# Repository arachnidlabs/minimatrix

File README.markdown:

# Minimatrix

Minimatrix is a teeny little backpack for 3cm monocolor LED matrixes. It plays animations, and is reprogrammable via your computer monitor!

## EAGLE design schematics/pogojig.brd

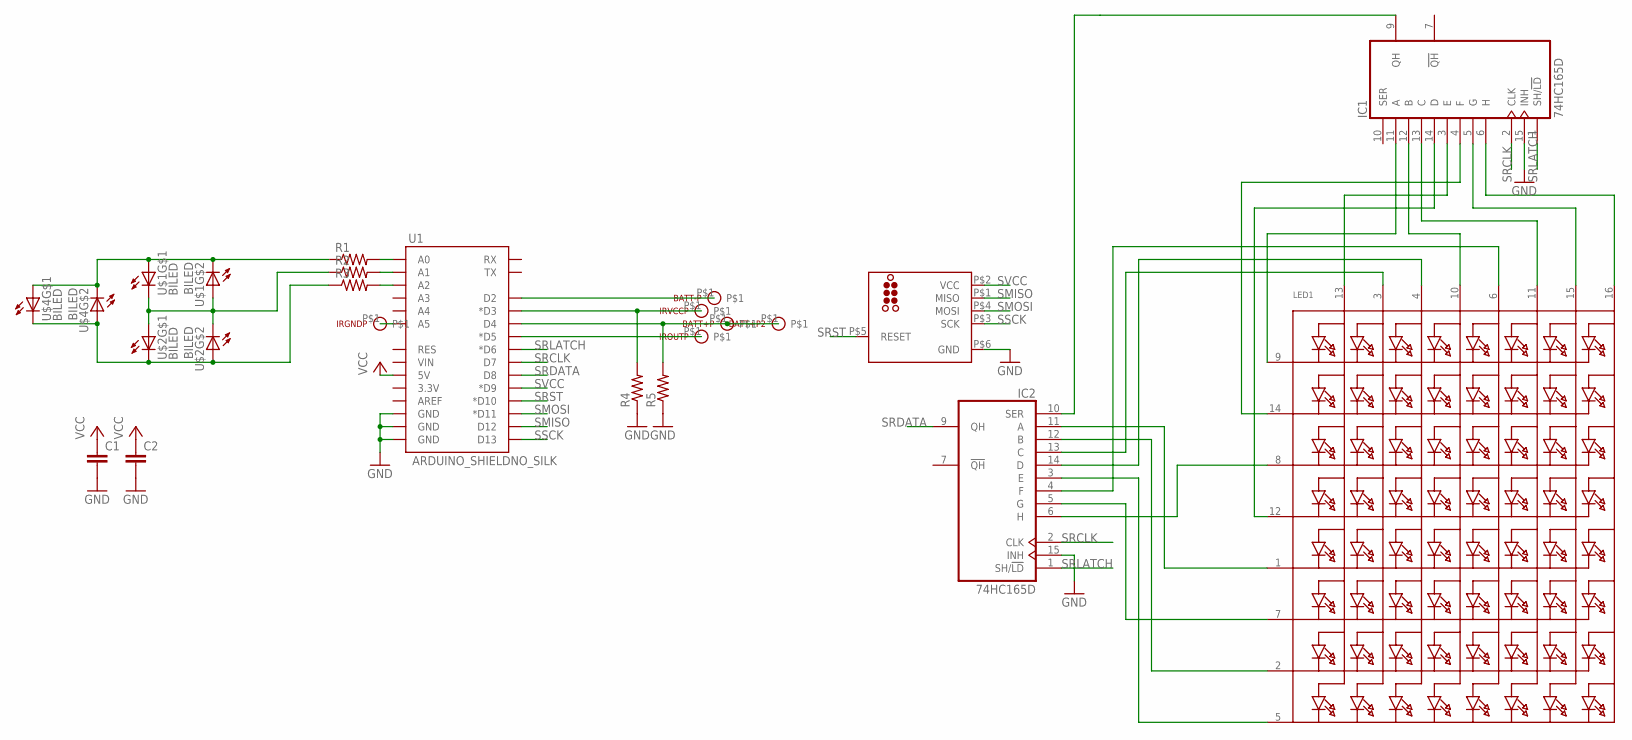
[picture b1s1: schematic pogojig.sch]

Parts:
BATT+P, BATT+P2: POGOPIN1.02; POGOPIN-1.02
BATT-P: POGOPIN1.02; POGOPIN-1.02
C1, C2: CAP0805; 0805
IC1, IC2: 74HC165D; SO16
IRGNDP: POGOPIN1.02; POGOPIN-1.02
IROUTP: POGOPIN1.02; POGOPIN-1.02
IRVCCP: POGOPIN1.02; POGOPIN-1.02
LED1: SEGMENT_8X8_ROWCATHODE; SEGMENT-30MM-POGO
R1, R2, R3, R4, R5: RESISTOR0805-RES; 0805
U1: ARDUINO_SHIELDNO_SILK; DUEMILANOVE_VIAS
U$1, U$2, U$4: BILED
U$3: TC2030_AVR; TC2030-MCP-NL-POGO

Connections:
GND: C1.2, C2.2, IC1.8 (GND), IC1.15 (INH), IC2.8 (GND), IC2.15 (INH), R4.1, R5.1, U1.GND@0 (GND), U1.GND@1 (GND), U1.GND@2 (GND), U$3.P$6 (GND)
unnamed: IC2.11 (A), LED1.1 (K5)
unnamed: IC2.12 (B), LED1.2 (K7)
unnamed: IC2.13 (C), LED1.3 (A2)
unnamed: IC2.14 (D), LED1.4 (A3)
unnamed: IC2.3 (E), LED1.5 (K8)
unnamed: IC2.4 (F), LED1.6 (A5)
unnamed: IC1.14 (D), LED1.12 (K4)
unnamed: IC2.5 (G), LED1.7 (K6)
unnamed: IC2.6 (H), LED1.8 (K3)
unnamed: IC1.11 (A), LED1.9 (K1)
unnamed: IC1.12 (B), LED1.10 (A4)
unnamed: IC1.13 (C), LED1.11 (A6)
unnamed: IC1.3 (E), LED1.13 (A1)
unnamed: IC1.4 (F), LED1.14 (K2)
unnamed: IC1.5 (G), LED1.15 (A7)
unnamed: IC1.6 (H), LED1.16 (A8)
unnamed: IC1.9 (QH), IC2.10 (SER)
unnamed: IRGNDP.P$1, U1.A5
unnamed: BATT+P.P$1, BATT+P2.P$1, R5.2, U1.D4
unnamed: BATT-P.P$1, U1.D2
unnamed: IRVCCP.P$1, R4.2, U1.D3 (*D3)
unnamed: IROUTP.P$1, U1.D5 (*D5)
unnamed: R3.2, U1.A2
unnamed: R2.2, U1.A1
unnamed: R1.2, U1.A0
unnamed: R3.1, U$2.A2 (A), U$2.C1 (C), U$4.A2 (A), U$4.C1 (C)
unnamed: R1.1, U$1.A1 (A), U$1.C2 (C), U$4.A1 (A), U$4.C2 (C)
unnamed: R2.1, U$1.A2 (A), U$1.C1 (C), U$2.A1 (A), U$2.C2 (C)
SMISO: U1.D12, U$3.P$1 (MISO)
SMOSI: U1.D11 (*D11), U$3.P$4 (MOSI)
SRCLK: IC1.2 (CLK), IC2.2 (CLK), U1.D7
SRDATA: IC2.9 (QH), U1.D8
SRLATCH: IC1.1 (SH/!LD), IC2.1 (SH/!LD), U1.D6 (*D6)
SRST: U1.D10 (*D10), U$3.P$5 (RESET)
SSCK: U1.D13, U$3.P$3 (SCK)
SVCC: U1.D9 (*D9), U$3.P$2 (VCC)
VCC: C1.1, C2.1, IC1.16 (VCC), IC2.16 (VCC), U1.5V

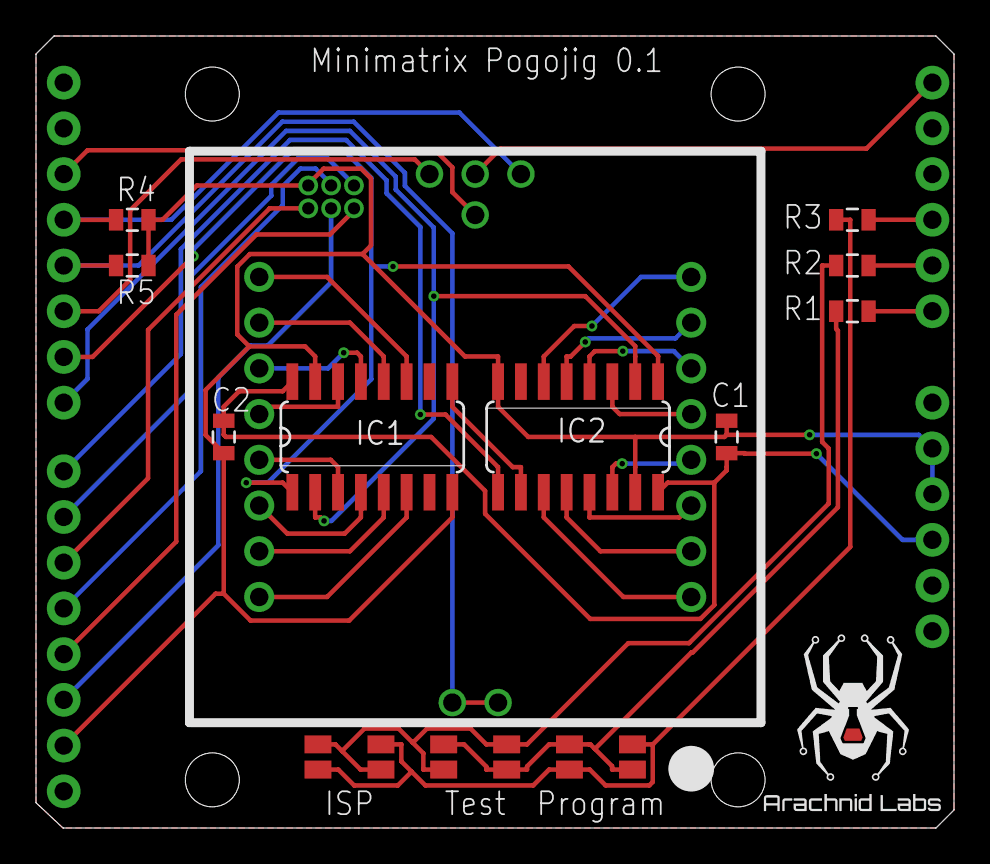
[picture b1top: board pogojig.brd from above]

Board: 2 copper layers, 51.0 x 44.0 mm, 22 parts (1 on the bottom side), 38 nets.

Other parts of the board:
U$5: ARACHNID_LABS_LOGO_SM

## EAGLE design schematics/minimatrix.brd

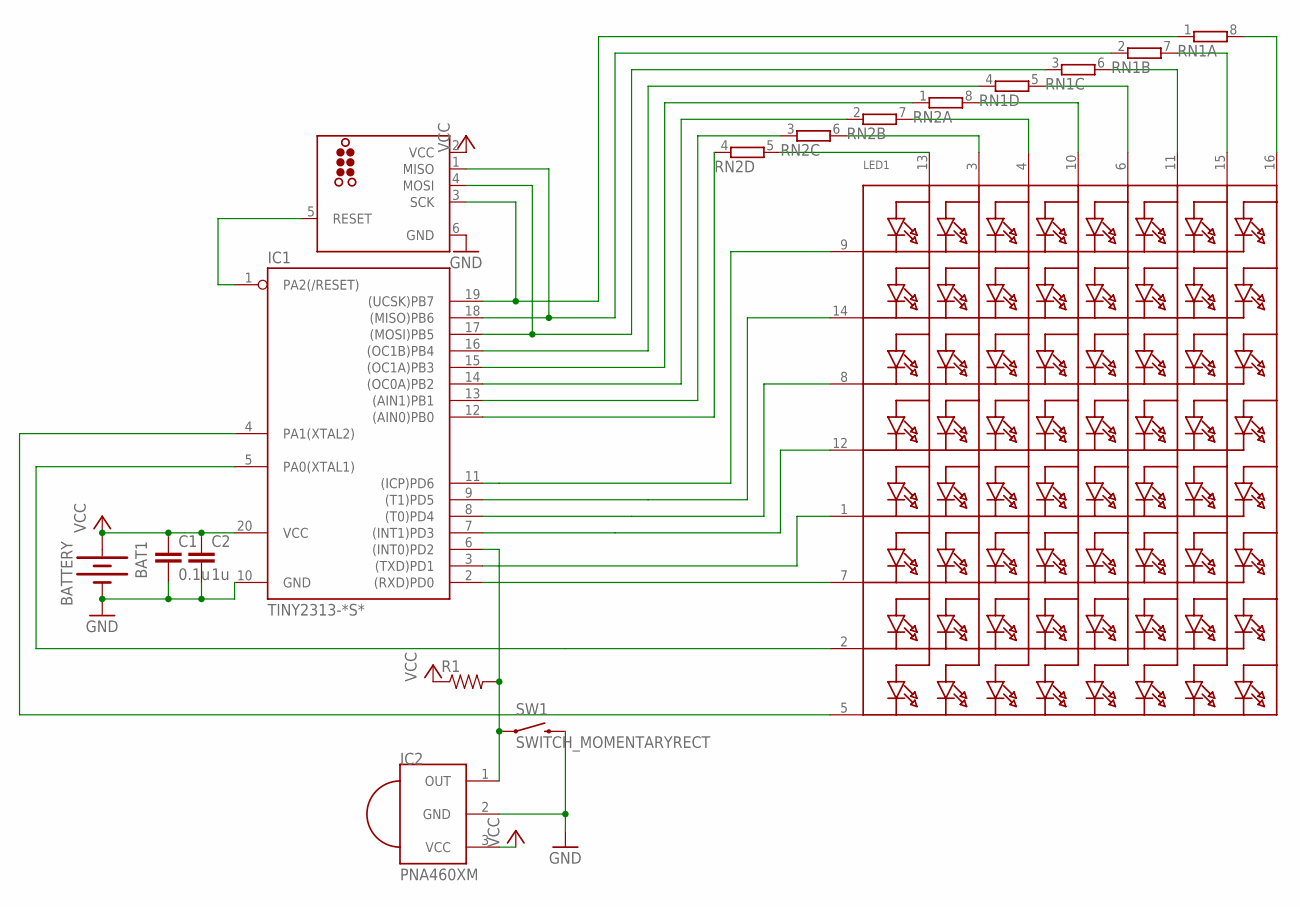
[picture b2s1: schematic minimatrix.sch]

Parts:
BAT1: BATTERY; COINCELL_PTH
C1: 0.1u; 0805
C2: 1u; 0805
IC1: TINY2313-*S*; SO20L$
IC2: PNA460XM
LED1: SEGMENT_8X8_ROWCATHODEM12A881UR; SEGMENT_BL-M12A881UR
R1: RESISTOR0805-RES; 0805
RN1, RN2: 4R-NCAY16; CAY16
SW1: SWITCH_MOMENTARYRECT; SWITCH_MOMENTARY_RECT
U$3: TC2030_AVRMCP-NL; TC2030-MCP-NL

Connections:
C2: IC1.13 ((AIN1)PB1), RN2.3 (1)
C3: IC1.14 ((OC0A)PB2), RN2.2 (1)
C4: IC1.15 ((OC1A)PB3), RN2.1
C5: IC1.16 ((OC1B)PB4), RN1.4 (1)
COL1: IC1.12 ((AIN0)PB0), RN2.4 (1)
GND: BAT1.NEG (-), C1.2, C2.2, IC1.10 (GND), IC2.2 (GND), SW1.P$2 (2), U$3.6 (GND)
MISO: IC1.18 ((MISO)PB6), RN1.2 (1), U$3.1 (MISO)
MOSI: IC1.17 ((MOSI)PB5), RN1.3 (1), U$3.4 (MOSI)
unnamed: IC1.2 ((RXD)PD0), LED1.7 (K6)
unnamed: LED1.3 (A2), RN2.6 (2)
unnamed: LED1.4 (A3), RN2.7 (2)
unnamed: LED1.10 (A4), RN2.8 (2)
unnamed: LED1.6 (A5), RN1.5 (2)
unnamed: LED1.11 (A6), RN1.6 (2)
unnamed: LED1.15 (A7), RN1.7 (2)
unnamed: LED1.16 (A8), RN1.8 (2)
unnamed: LED1.13 (A1), RN2.5 (2)
unnamed: IC1.3 ((TXD)PD1), LED1.1 (K5)
unnamed: IC1.4 (PA1(XTAL2)), LED1.5 (K8)
unnamed: IC1.6 ((INT0)PD2), IC2.1 (OUT), R1.2, SW1.P$1 (1)
R2: IC1.9 ((T1)PD5), LED1.14 (K2)
R3: IC1.8 ((T0)PD4), LED1.8 (K3)
R4: IC1.7 ((INT1)PD3), LED1.12 (K4)
R7: IC1.5 (PA0(XTAL1)), LED1.2 (K7)
RESET: IC1.1 (PA2(/RESET)), U$3.5 (RESET)
ROW1: IC1.11 ((ICP)PD6), LED1.9 (K1)
SCK: IC1.19 ((UCSK)PB7), RN1.1, U$3.3 (SCK)
VCC: BAT1.POS1 (+), BAT1.POS2 (+), C1.1, C2.1, IC1.20 (VCC), IC2.3 (VCC), R1.1, U$3.2 (VCC)

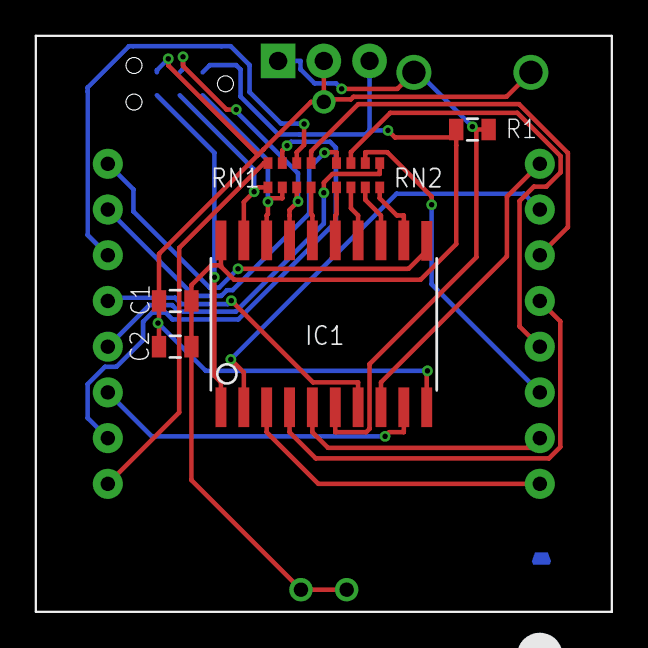
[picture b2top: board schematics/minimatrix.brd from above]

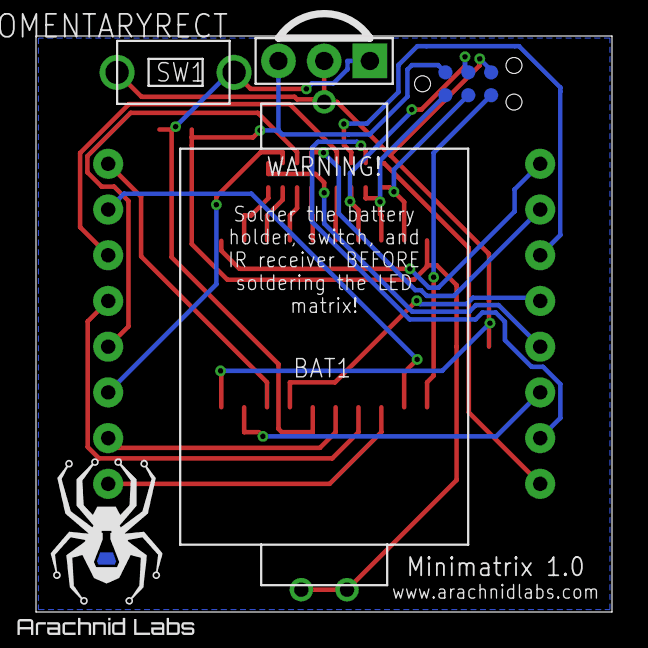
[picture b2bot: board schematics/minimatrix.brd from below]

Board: 2 copper layers, 32.0 x 32.0 mm, 12 parts (5 on the bottom side), 28 nets.

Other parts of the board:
U$4: ARACHNID_LABS_LOGO_SM

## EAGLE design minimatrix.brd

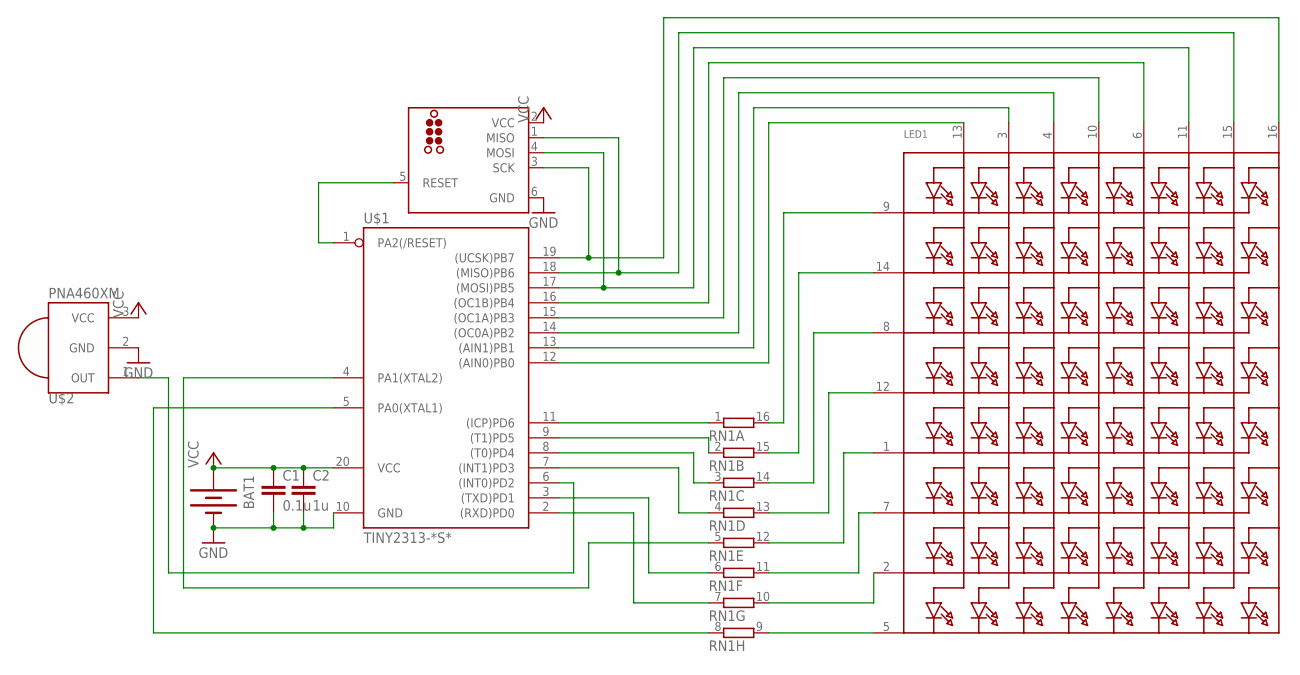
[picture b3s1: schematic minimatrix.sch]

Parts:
BAT1: BATTERY20MM_4LEGS; BATTCON_20MM_4LEGS
C1: 0.1u; 0805
C2: 1u; 0805
LED1: SEGMENT_8X8_ROWCATHODEM12A881UR; SEGMENT_BL-M12A881UR
RN1: 8R-NEXB2HV; EXB2HV
U$1: TINY2313-*S*; SO20L$
U$2: PNA460XM
U$3: TC2030_AVRMCP-NL; TC2030-MCP-NL

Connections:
C1: LED1.13 (A1), U$1.12 ((AIN0)PB0)
C2: LED1.3 (A2), U$1.13 ((AIN1)PB1)
C3: LED1.4 (A3), U$1.14 ((OC0A)PB2)
C4: LED1.10 (A4), U$1.15 ((OC1A)PB3)
C5: LED1.6 (A5), U$1.16 ((OC1B)PB4)
C6: LED1.11 (A6), U$1.17 ((MOSI)PB5), U$3.4 (MOSI)
C7: LED1.15 (A7), U$1.18 ((MISO)PB6), U$3.1 (MISO)
C8: LED1.16 (A8), U$1.19 ((UCSK)PB7), U$3.3 (SCK)
GND: BAT1.2 (-), C1.2, C2.2, U$1.10 (GND), U$2.2 (GND), U$3.6 (GND)
unnamed: U$1.6 ((INT0)PD2), U$2.1 (OUT)
unnamed: U$1.1 (PA2(/RESET)), U$3.5 (RESET)
unnamed: RN1.5 (1), U$1.4 (PA1(XTAL2))
R1: RN1.1, U$1.11 ((ICP)PD6)
R2: RN1.2 (1), U$1.9 ((T1)PD5)
R3: RN1.3 (1), U$1.8 ((T0)PD4)
R4: RN1.4 (1), U$1.7 ((INT1)PD3)
R6: RN1.6 (1), U$1.3 ((TXD)PD1)
R7: RN1.7 (1), U$1.2 ((RXD)PD0)
R8: RN1.8 (1), U$1.5 (PA0(XTAL1))
ROW1: LED1.9 (K1), RN1.16 (2)
ROW2: LED1.14 (K2), RN1.15 (2)
ROW3: LED1.8 (K3), RN1.14 (2)
ROW4: LED1.12 (K4), RN1.13 (2)
ROW5: LED1.1 (K5), RN1.12 (2)
ROW6: LED1.7 (K6), RN1.11 (2)
ROW7: LED1.2 (K7), RN1.10 (2)
ROW8: LED1.5 (K8), RN1.9 (2)
VCC: BAT1.1 (+), C1.1, C2.1, U$1.20 (VCC), U$2.3 (VCC), U$3.2 (VCC)

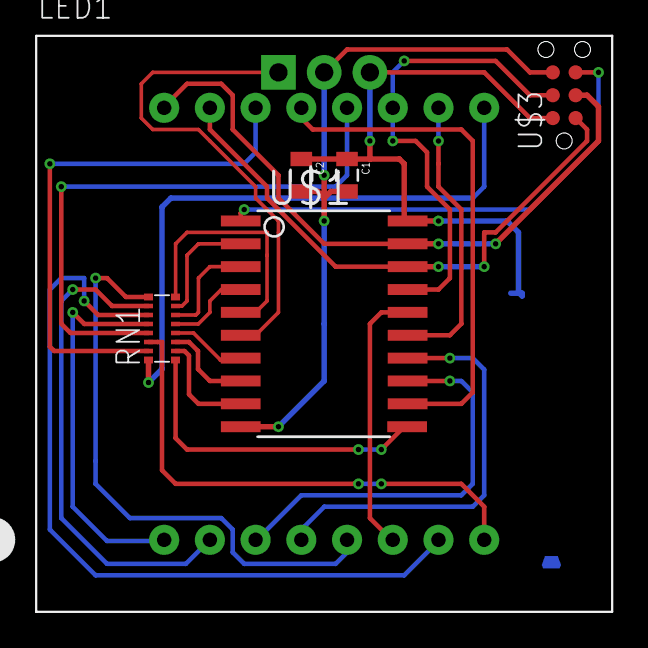
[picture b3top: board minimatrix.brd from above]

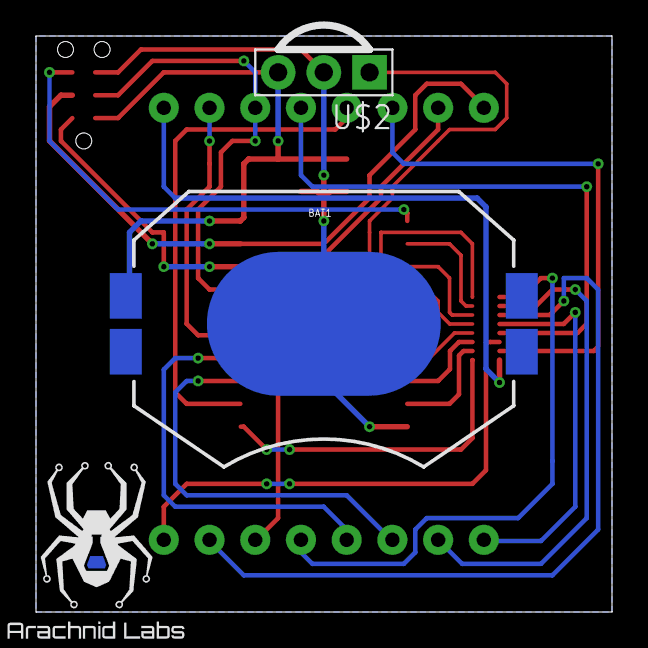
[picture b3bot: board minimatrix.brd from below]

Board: 2 copper layers, 32.0 x 32.0 mm, 9 parts (3 on the bottom side), 28 nets.

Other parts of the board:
U$4: ARACHNID_LABS_LOGO_SM

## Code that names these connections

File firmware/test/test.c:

#define F_CPU 8000000UL  // 8 MHz

#include <inttypes.h>
#include <avr/io.h>
#include <avr/pgmspace.h>
#include <avr/sleep.h>
#include <util/delay.h>
#include <avr/interrupt.h>

#include "../src/hardware.h"

static void ioinit(void) {
	// Set rows and columns as output
	COLUMN_DDR = 0xff;
	DDRD |= PORTD_ROWS;
	DDRA |= PORTA_ROWS;
//	PORTB = 0x255;
//	PORTD |= PORTD_ROWS;
//	PORTA |= PORTA_ROWS;

	sei();
}

struct {
	volatile uint8_t *port;
	uint8_t pin;
} out_pins[] = {
	{&PORTD, _BV(PD1)},
	{&PORTA, _BV(PA0)},
	{&PORTB, _BV(PB1)},
	{&PORTB, _BV(PB2)},
	{&PORTA, _BV(PA1)},
	{&PORTB, _BV(PB4)},
	{&PORTD, _BV(PD0)},
	{&PORTD, _BV(PD4)},
	{&PORTD, _BV(PD6)},
	{&PORTB, _BV(PB3)},
	{&PORTB, _BV(PB5)},
	{&PORTD, _BV(PD3)},
	{&PORTB, _BV(PB0)},
	{&PORTD, _BV(PD5)},
	{&PORTB, _BV(PB6)},
	{&PORTB, _BV(PB7)},
};

static uint8_t num_pins = 16;

void main(void) __attribute__((noreturn));

void main(void) {
	ioinit();

	int idx = 6;
	while(1) {
		// Wait for rising edge on IR PIN
		while(!(PIND & _BV(IR_PIN)));

		*out_pins[idx].port &= ~out_pins[idx].pin;
		idx = (idx + 1) % num_pins;
		*out_pins[idx].port |= out_pins[idx].pin;

		// Wait for falling edge on IR PIN
		while(PIND & _BV(IR_PIN));
	}
}

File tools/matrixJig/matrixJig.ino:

// Standalone AVR ISP programmer
// Modified July 2013 by Nick Johnson <nick@arachnidlabs.com>
// August 2011 by Limor Fried / Ladyada / Adafruit
// Jan 2011 by Bill Westfield ("WestfW")
//
// this sketch allows an Arduino to program a flash program
// into any AVR if you can fit the HEX file into program memory
// No computer is necessary. Two LEDs for status notification
// Press button to program a new chip. Piezo beeper for error/success 
// This is ideal for very fast mass-programming of chips!
//
// It is based on AVRISP
//
// using the following pins:
// 10: slave reset
// 11: MOSI
// 12: MISO
// 13: SCK
// ----------------------------------------------------------------------
#include <avr/pgmspace.h>
#include "optiLoader.h"
#include "SPI.h"

// Global Variables
int pmode=0;
byte pageBuffer[64];		       /* One page of flash */


/*
 * Pins to target
 */
#define SCK 13
#define MISO 12
#define MOSI 11
#define RESET 10
#define TARGET_POWER 9

#define PIN_BATT_NEG 2
#define PIN_BATT_POS 4
#define PIN_IRVCC 3
#define PIN_IROUT 5
#define PIN_SRLATCH 6
#define PIN_SRCLK 7
#define PIN_SRDATA 8

#define ISP_OK A2, A1, A0
#define ISP_BAD A1, A2, A0
#define TEST_OK A1, A0, A2
#define TEST_BAD A0, A1, A2
#define PROG_OK A2, A0, A1
#define PROG_BAD A0, A2, A1

void slow_down(boolean enable) {
  static uint16_t saved_ubrr;
  static boolean slow = false;

  // If we're already in the mode we're asking for, do nothing.  
  if(enable == slow) return;
  
  cli();
  if(enable) {
    CLKPR = _BV(CLKPCE);
    CLKPR = 0x1;
    saved_ubrr = (UBRR0H << 8) | UBRR0L;
    UBRR0H = saved_ubrr >> 9;
    UBRR0L = (saved_ubrr >> 1) & 0xFF;
    slow = true;
  } else {
    CLKPR = _BV(CLKPCE);
    CLKPR = 0x0;
    UBRR0H = saved_ubrr >> 8;
    UBRR0L = saved_ubrr & 0xFF;
    slow = false;
  }
  sei();
}

void setup () {
  Serial.begin(57600);			/* Initialize serial for status msgs */
  Serial.println("\nMatrixjig Bootstrap programmer (originally OptiLoader Bill Westfield (WestfW))");

  pinMode(TARGET_POWER, OUTPUT);
  pinMode(PIN_SRLATCH, OUTPUT);
  pinMode(PIN_SRCLK, OUTPUT);
  pinMode(PIN_SRDATA, INPUT);
  pinMode(PIN_IROUT, OUTPUT);
  digitalWrite(PIN_SRLATCH, HIGH);

  pulse(ISP_OK, 2);
  pulse(TEST_OK, 2);
  pulse(PROG_OK, 2);
  pulse(ISP_BAD, 2);
  pulse(TEST_BAD, 2);
  pulse(PROG_BAD, 2);  
}

boolean do_fuses(image_t *image) {
  delay(10);
  if (! programFuses(image->image_progfuses)) {
    error("Failed to program fuses");
    return false;
  }
  delay(10);
  if (! verifyFuses(image->image_progfuses, image->fusemask) ) {
    error("Failed to verify fuses");
    return false;
  }

  return true;
}

boolean do_program(image_t *image) {
  const unsigned char *imagedata = (const unsigned char*)pgm_read_word(&image->image_data);
  uint8_t pagesize = pgm_read_byte(&image->image_pagesize);
  uint16_t chipsize = pgm_read_word(&image->chipsize);
  
  programImage(imagedata, pagesize, chipsize);
  
  end_pmode();
  start_pmode();
  
  Serial.println("\nVerifing flash...");
  if (! verifyImage(imagedata, chipsize) ) {
    error("Failed to verify chip");
    return false;
  } else {
    Serial.println("\tFlash verified correctly!");
  }
  return true;
}

boolean load_test_program() {
  image_t *testimage;
  if (! (testimage = findImage("test.hex"))) {
    error("Failed to load test image");
    return false;
  }
  
  slow_down(true);
  target_poweron();

  uint16_t signature = pgm_read_word(&testimage->image_chipsig);
        
  if (signature != readSignature()) {
    error("Invalid signature");
    return false;
  }
  
  eraseChip();

  if(!do_fuses(testimage))
    return false;

  slow_down(false);

  end_pmode();
  start_pmode();
  
  if(!do_program(testimage))
    return false;

  end_pmode();
    
  return true;
}

boolean run_tests() {
  delay(200);
  for(int i = 0; i < 16; i++) {
    digitalWrite(PIN_IROUT, HIGH);
    digitalWrite(PIN_SRLATCH, LOW);
    delay(1);
    digitalWrite(PIN_SRLATCH, HIGH);
    uint16_t incoming = digitalRead(PIN_SRDATA);
    incoming |= shiftIn(PIN_SRDATA, PIN_SRCLK, MSBFIRST) << 8;
    incoming |= shiftIn(PIN_SRDATA, PIN_SRCLK, MSBFIRST);
    Serial.println(incoming, HEX);
    if(incoming != (1 << i)) {
      Serial.print("Expected 0x");
      Serial.print(1 << i, HEX);
      Serial.print(" but got 0x");
      Serial.println(incoming);
      return false;
    }

    digitalWrite(PIN_IROUT, LOW);
    delay(1);
  }
  return true;
}

boolean load_main_program() {
  image_t *mainimage;
  if(!(mainimage = findImage("minimatrix.hex"))) {
    error("Failed to load main image");
    return false;
  }
  
  start_pmode();
  eraseChip();
  end_pmode();
  
  start_pmode();
  if(!do_program(mainimage))
    return false;
    
  const unsigned char *eepromdata = (const unsigned char*)pgm_read_word(&mainimage->eeprom_data);
  uint8_t pagesize = pgm_read_byte(&mainimage->eeprom_pagesize);
  uint16_t eepromsize = pgm_read_word(&mainimage->eepromsize);
  Serial.println("Programming EEPROM...");
  if(!programEEPROM(eepromdata, pagesize, eepromsize))
    return false;
    
  Serial.println("Verifying EEPROM...");
  if(!verifyEEPROM(eepromdata, eepromsize))
    return false;
    
  end_pmode();
  
  return true;
}

boolean program_and_test() {
  if(load_test_program()) {
    led_on(ISP_OK);
  } else {
    led_on(ISP_BAD);
    return false;
  }

  if(run_tests()) {
    led_on(TEST_OK);
  } else {
    led_on(TEST_BAD);
    return false;
  }

  if(load_main_program()) {
    led_on(PROG_OK);
  } else {
    led_on(PROG_BAD);
    return false;
  }
  
  return true;
}

void loop (void) {
  digitalWrite(TARGET_POWER, HIGH);			/* Turn on target power */

  Serial.println("\nType 'G' or hit BUTTON for next chip");
  while (1) {
    if  (Serial.read() == 'G')
      break;  
    if(digitalRead(PIN_BATT_POS))
      break;
  }
  delay(1000);

  if(program_and_test()) {
    Serial.println("PASS");
  } else {
    Serial.println("FAIL");
  }
  delay(1000);
  while(digitalRead(PIN_BATT_POS));
 
  target_poweroff();			/* turn power off */
  leds_off(ISP_OK);
}

void error(char *string) { 
  slow_down(false);
  Serial.println(string); 
}

void start_pmode () {
  pinMode(13, INPUT); // restore to default

  SPI.begin();
  SPI.setClockDivider(SPI_CLOCK_DIV128); 
  
  debug("...spi_init done");
  // following delays may not work on all targets...
  pinMode(RESET, OUTPUT);
  digitalWrite(RESET, HIGH);
  pinMode(SCK, OUTPUT);
  digitalWrite(SCK, LOW);
  delay(50);
  digitalWrite(RESET, LOW);
  delay(50);
  pinMode(MISO, INPUT);
  pinMode(MOSI, OUTPUT);
  debug("...spi_transaction");
  spi_transaction(0xAC, 0x53, 0x00, 0x00);
  debug("...Done");
  pmode = 1;
}

void end_pmode () {
  SPCR = 0;				/* reset SPI */
  digitalWrite(MISO, 0);		/* Make sure pullups are off too */
  pinMode(MISO, INPUT);
  digitalWrite(MOSI, 0);
  pinMode(MOSI, INPUT);
  digitalWrite(SCK, 0);
  pinMode(SCK, INPUT);
  digitalWrite(RESET, HIGH);
  //pinMode(RESET, INPUT);
  pmode = 0;
}


/*
 * target_poweron
 * begin programming
 */
boolean target_poweron ()
{
  digitalWrite(RESET, LOW);  // reset it right away.
  pinMode(RESET, OUTPUT);
//  digitalWrite(TARGET_POWER, HIGH);
//  delay(100);
  Serial.print("Starting Program Mode");
  start_pmode();
  Serial.println(" [OK]");
  return true;
}

boolean target_poweroff ()
{
  end_pmode();
  digitalWrite(TARGET_POWER, LOW);
  return true;
}

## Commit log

2013-02-17 Initial commit.
2013-02-17 Rearrange pins so the IR receiver is on an interrupt.
2013-02-18 Rewire with fixed pinouts and better connection for IR receiver.
2013-03-08 Reorganized repo; added initial firmware
2013-03-10 Sense light levels and display them on LEDs
2013-03-10 Added LCD font and scrolling demo for it
2013-03-14 Added LCD font and IR control
2013-03-14 Modified null character in default font
2013-03-14 Update design restoring IR receiver.
2013-03-14 Scroll left/right when changing characters in edit mode (maybe).
2013-03-15 Add support for animations to minimatrix; first version of gif2matrix.py.
2013-03-15 Added animation support, other optimisations
2013-03-16 Refactored IR decoding into the ISR
2013-03-16 Minor tweaks
2013-03-16 Back to 4khz
2013-03-16 Refactored common code out into functions
2013-03-16 Much better keypress/repeat handling
2013-03-17 Added menu system, refactored into two separate ISRs
2013-03-18 Changes for powerdown mode
2013-03-18 Finally add glyphs
2013-03-18 Interim hack for (not really) sleep mode
2013-04-05 Tweaks for production version
2013-07-01 Numerous changes and improvements
2013-07-01 Invert font
2013-07-02 Initial version of adaloader
2013-07-07 Work on programmer code; don't accept commands when asleep
2013-07-07 Modify programmer sketch to work on the ATTiny4313
2013-07-08 Add support to makefile for generating binary outputs.
2013-07-08 More work on programming jig code
2013-07-08 Pogojig design files
2013-07-08 Add support for C definition outputs for images
2013-07-08 Refactor into src and test subfolders
2013-07-08 Refactor programming sketch to use binary data.
2013-07-08 Test program
2013-07-09 Refactored programmer code, added testing
2013-07-09 Fix programmer fuse writing by adding delays between fuses
2013-07-09 EEPROM programming, and ALL DONE\!
2013-07-12 More refactoring
2013-07-12 Changed command definitions to suit new remote
2013-07-12 When a user tries to edit an animation, give them a blank marquee instead
2013-07-12 Don't wrap around when paging through characters
2013-07-12 Fix eeprom write command
2013-07-12 Preserve marquee position, and reset it when entering edit mode
2013-07-12 Solved toggling issue
2013-07-12 Add support for double-buffering
2013-08-31 Made the script executable, since otherwise it won't build.
2013-08-31 A bunch of micro-edits to try to shrink the resulting binary.
    - Make all local functions static.
    - Make all loops use uint8_t for the index if possible.
    - Make variables and data const when possible.
    Seems to gain ~3% on the final ELF, not a lot but also not intrusive at all.
2013-09-01 Use slower SPI
2014-02-28 Made repeat_countdown unsigned, shaved off 2 bytes of code.
2014-02-28 Squashed display-writing together, shaved off another two bytes of code.
    I think I'm still OK with this, it uses ?: instead of if/else but it's pretty clear.
2014-02-28 Removed local functions, seems to drop code size by quite a bit.
2014-03-01 Renamed for better GitHub integration.
2014-05-08 Update main.c
    Added extended command to reload the config without having to pull the battery

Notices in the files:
parts and their libraries:
SparkFun-Electromechanical: Licensing: CC v3.0 Share-Alike You are welcome to use this library for commercial purposes.
tag-connect: ©2009 ROFA.cz - modified and updated by Robert Darlington ‹rdarlington@gmail.com›
